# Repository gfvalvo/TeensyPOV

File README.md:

# TeensyPOV:

## POV Project on Teensy 3.2 - WORK IN PROGRESS

Library for POV (Persistence of Vision) display using Teensy 3.2 board and Adafuit DotStar LEDs (APA102). Descriptions of the hardware (including schematics and PWB) are in the Hardware folder.
The library is configured to support up to 48 LEDs in the string and up to 512 angular positions (~0.7 degree resolution). These positions are referred to as "segments" in the code and description below.
## Sample Images:

[Video of POV in Action](https://youtu.be/CiRSouhlJos)

Note that interaction between the video's frame rate and the LED refresh rate causes some artifacts that aren't really there when you view the POV in person.

## Library Description:
Code in this library directly manipulates the Teensy processor's Programmable Interrupt Timers. Thus, it is incompatible with any code that uses these timers directly or indirectly via the Teensyduino IntervalTimer class.

All of the following class methods are demonstrated in the example sketches.
### Classes:
#### Class TeensyPOV
This class interfaces with the hardware and controls the LEDs to produce the POV display. All methods in this class are static. Thus there is no need to instantiate an object of this type.
#### Public TeensyPOV Members Functions:
****Initialize the T3.2 hardware needed for the POV Display****

    bool povSetup(uint8_t hPin, CRGB *ledPtr, uint8_t num)
**Arguments:**
 - **uint8_t hPin** - Hardware pin that the Hall Effect Sensor is connected to.
 - **CRGB \*ledPtr** - Pointer to an array of FastLED CRGB objects. These objects should be registered with the FastLED library before calling povSetup.
 - **uint8_t num** - Number LEDs in the array
 
****Check if Rotation Speed is High Enough for POV Display****

    bool rpmGood(void) 

****Get Number of Segments in the Currently Active POV Display.****

    uint16_t getNumSegments(void)

****Get Number of Teensy 3.2 PIT Ticks that Occurred During the Blade's last Rotation Period. On a 96 MHz T3.2 there are 48,000,000 Ticks per Second.****

    uint32_t getLastRotationCount(void)

****Set the color of an LED directly on the display.****

    void setPixel(uint16_t segment, uint16_t pixel, uint32_t value)

**Arguments:**

- **uint16_t segment** - Rotational segment of the LED, counted clockwise from Top Dead Center. Value between 0 and (Number of Segments)-1
- **uint16_t pixel** - Radial position of the LED, 0 = innermost.
- **uint32_t value** - Color of the LED expressed as index into current Palette.

#### Public TeensyPOV Data Members:

Defined constants that can be used in calls to TeensyPovDisplay methods (see **Class TeensyPovDisplay**):
```
static const uint8_t LOG_2_SEGMENTS = 1;
static const uint8_t LOG_4_SEGMENTS = 2;
static const uint8_t LOG_8_SEGMENTS = 3;
static const uint8_t LOG_16_SEGMENTS = 4;
static const uint8_t LOG_32_SEGMENTS = 5;
static const uint8_t LOG_64_SEGMENTS = 6;
static const uint8_t LOG_128_SEGMENTS = 7;
static const uint8_t LOG_256_SEGMENTS = 8;
static const uint8_t LOG_512_SEGMENTS = 9;

static const uint8_t COLOR_BITS_1 = 1;
static const uint8_t COLOR_BITS_2 = 2;
static const uint8_t COLOR_BITS_4 = 4;
static const uint8_t COLOR_BITS_8 = 8;
```
#### Class TeensyPovDisplay
This class allows the user to define POV images to be displayed. There can be multiple instances of this class defining different images. Only one is actively displayed at a time.
#### Public TeensyPovDisplay Members Functions:
****Constructor.****
````
TeensyPovDisplay()
````
****Load an empty TeensyPovDisplay object. Would be used if no bitmap image or text is desired. Pixels would be set by the main program using the setLed() method.****
````
void load(void)
````
****Load a TeensyPovDisplay object with a bit pattern image.****
````
void load(const LedArrayStruct *pattern)
````

**Arguments:**

- **const LedArrayStruct \*pattern** - Pointer to the image structure. The struct pointed to must be static or global. See below for definition of the LedArrayStruct structure.

****Load a TeensyPovDisplay object with text strings.****
````
void load(const DisplayStringSpec *strArray, uint8_t n)
````
**Arguments:**
- **const DisplayStringSpec \*strArray** - Pointer to an array of DisplayStringSpec structures. The array pointed to must be static or global. See below for definition of the DisplayStringSpec structure.
- **uint8_t n** - Number of DisplayStringSpec structures in the array.

****Load a TeensyPovDisplay object with a bit pattern image and text strings.****
````
void load(const LedArrayStruct *pattern, const DisplayStringSpec *strArray, uint8_t n)
````
**Arguments:**
- **const LedArrayStruct \*pattern** - Pointer to the image structure. The struct pointed to must be static or global. See below for definition of the LedArrayStruct structure.
- **const DisplayStringSpec \*strArray** - Pointer to an array of DisplayStringSpec structures. The array pointed to must be static or global. See below for definition of the DisplayStringSpec structure.
- **uint8_t n** - Number of DisplayStringSpec structures in the array.

****Display a TeensyPovDisplay object on the POV LEDs. Resets the duration and rotation timers.****
````
void activate()
````
****Refresh the TeensyPovDisplay object on the POV LEDs after changing text, bit image, palette, etc. Does not reset the duration and rotation timers****
````
void refresh()
````
****Set the POV parameters for a TeensyPovDisplay object that does not contain a bitmap image (i.e. a LedArrayStruct). Call this function after load() and before activate()****
````
void setDisplay(uint8_t logSeg, uint8_t cBits, uint16_t tdc, const uint32_t *colors)
````
**Arguments:**
- **uint8_t logSeg** - Log (base 2) of number of TDC segments. Use static constants defined by class TeensyPOV.
- **uint8_t cBits** - Number of color bits. Use static constants defined by class TeensyPOV.
- **uint16_t tdc** - Segment number to display when rotating blade hits Top Dead Center.
- **const uint32_t \*colors** - Pointer to array defining RGB color pallet. Array must have at least 2 ^ cBits elements. The array pointed to must be static or global.

****Set timing for dynamic TeensyPovDisplay objects. Calling this function is optional, all values are set to their default values by the load() method.****
````
void setTiming(uint32_t duration, uint32_t rotation, int16_t tdcDelta)
````
**Arguments:**
- **uint32_t duration** - Time (in milliseconds) before the object expires. Use zero (default) if object is permanent.
- **uint32_t rotation** - Time (in milliseconds) between changes in the Top Dead Center segment, causes display to rotate. Use zero (default)  for no rotation.
- **int16_t tdcDelta** - Adjustment to Top Dead Center segment every 'rotation' milliseconds. Use negative value for clockwise rotation and positive value for anti-clockwise. Has no effect if 'rotation' is zero.

****Determine if duration of TeensyPovDisplay object has expired and performs specified rotation****
````
bool update()
````
**Returns:** True if display's time has expired.

****Set optional callback function to be called when a TeensyPovDisplay object is activated.****
````
void setActivationCallback(void (*ptr)(TeensyPovDisplay *))
````
**Arguments:**
- **void (\*ptr)(TeensyPOV \*)** - Pointer to the function to be called. The function must take as an argument a pointer to the TeensyPOV object that was activated and return void.

****Set optional callback function to be called when a TeensyPovDisplay object is updated.****
````
void setUpdateCallback(void (*ptr)(TeensyPovDisplay *))
````
**Arguments:**
- **void (\*ptr)(TeensyPOV \*)** - Pointer to the function to be called. The function must take as an argument a pointer to the TeensyPOV object that was updated and return void.

****Set optional callback function to be called when a TeensyPovDisplay object expires.****
````
void setExpireCallback(void (*ptr)(TeensyPovDisplay *))
````
**Arguments:**
- **void (\*ptr)(TeensyPOV \*)** - Pointer to the function to be called. The function must take as an argument a pointer to the TeensyPOV object that expired and return void.

#### Enums and Structures Defined by TeensyPOV Class:
****Identifies text position at top or bottom of display.****
````
enum TextPosition {TOP, BOTTOM};
````
****Specification for character string to be displayed.****
````
struct DisplayStringSpec {
	const char *characters;
	TextPosition position;
	uint8_t topRow;
	uint8_t textColor;
	uint8_t backgroundColor;
	bool invert;
};
````
- **const char \*characters** - Pointer to null-terminated char array.
- **TextPosition position** - Position where text will be displayed.
- **uint8_t topRow** - LED position (from center) for top row of characters. Minimum value is 6.
- **uint8_t textColors** - Color of text expressed as index into current Palette.
- **uint8_t backgroundColor** - Background color for text expressed as index into current Palette.
- **bool invert** - Flip text on bottom so it appears right-side-up.

****Specification for bit map image to be displayed.****
````
struct LedArrayStruct {
	const uint32_t *array;
	const uint32_t *colors;
	uint32_t numColorBits;
	uint8_t logNumSegments;
	uint32_t columns;
	uint32_t tdcDisplaySegment;
};
````
- **const uint32_t \*array** - Pointer to 2-dimensional bit map array. See below for specification. The array pointed to must be static or global.
- **const uint32_t \*colors** - Pointer to array defining RGB color pallet. Array must have at least 2 ^ numColorBits elements. The array pointed to must be static or global. 
- **uint32_t numColorBits** - Number of color bits. Use static constants defined by class TeensyPOV.
- **uint8_t logNumSegments** - Log (base 2) of number of TDC segments. Use static constants defined by class TeensyPOV.
- **uint32_t columns** - Number of columns in the array.
- **uint32_t tdcDisplaySegment** - Segment number to display when rotating blade hits Top Dead Center.
- 
****Bit Map Array****

The number of Rows is equal to the number of segments in the display. The number of Columns depends on how many color bits are used to represent each LED. For example, with 36 LEDs, Two Bits / LED, and 256 Segments:

## POV Hardware:
### Block Diagram:

### PWB Schematic:

### PWB Layout:

### Populated PWB:

### Blank Blade with Hub Mounted:

### Backside Components:

### Hall Sensor:

### LEDs Mounted:

### Start with this Fan
[$20 From Target](https://www.target.com/p/holmes-174-20-3-speed-box-fan-black-hbf2001d-b/-/A-15024768)

### Reverse these Rails as Shown to Push Motor Further out the Back.

### Reverse these Brackets as Shown to Push Motor Further out the Back.

### Hall device senses magnet and signal processor that LEDs are in the Top Dead Center position.

# CREDITS
I shamelessly appropriated the Dot Matrix characters that Arduino Forum user @Jiggy-Ninja developed for his POV project posted here:
[Dram Queen](https://forum.arduino.cc/index.php?topic=493075.0)

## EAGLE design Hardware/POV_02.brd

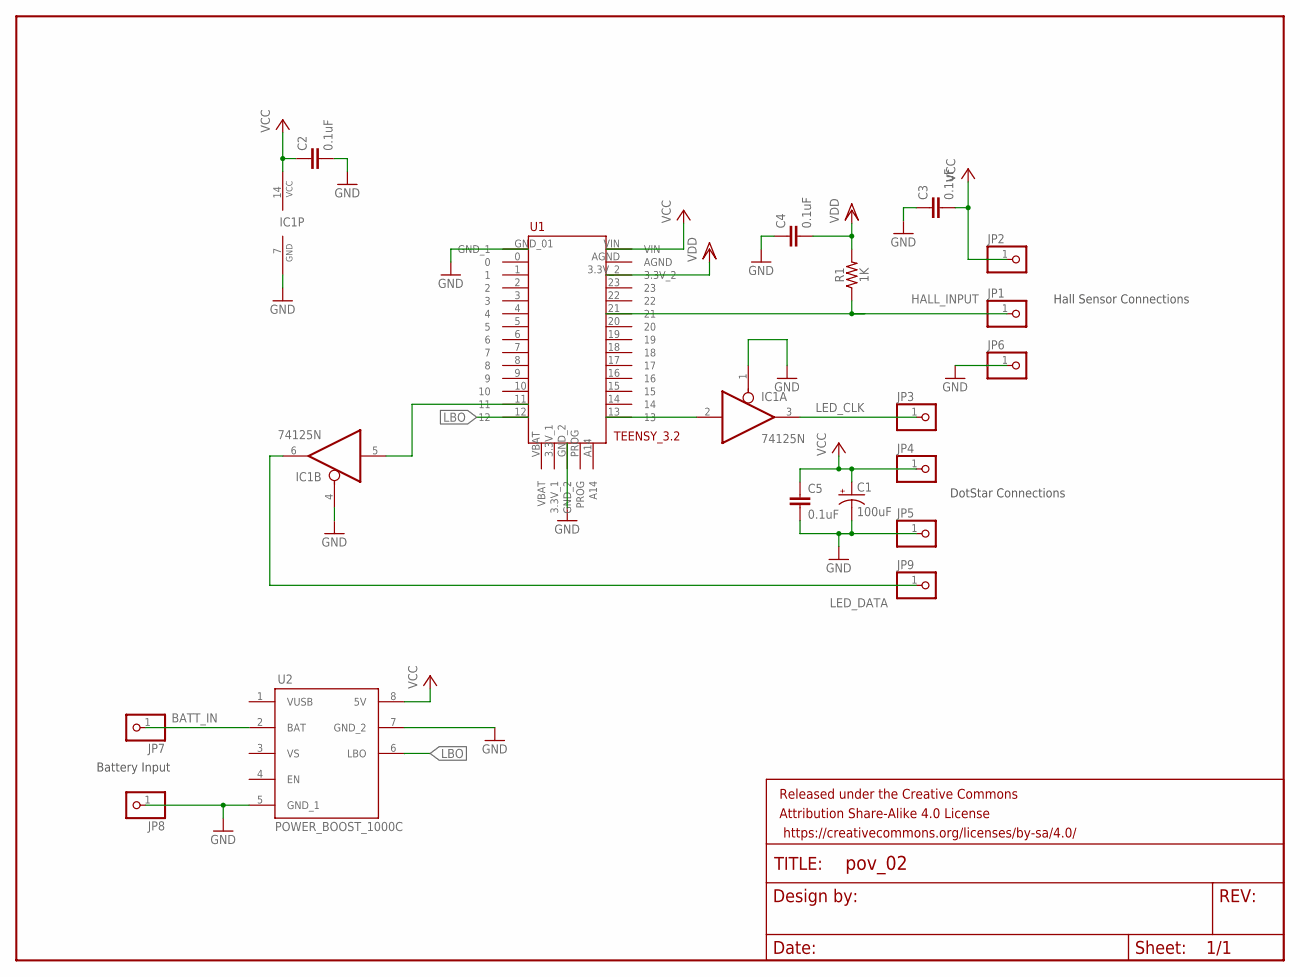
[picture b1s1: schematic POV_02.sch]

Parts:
C1: 100uF; CPOL-RADIAL-2.5MM-6.5MM
C2, C3, C4, C5: 0.1uF; CAP-PTH-SMALL-KIT
FRAME1: FRAME-LETTERNO_PACKAGE; DUMMY
IC1: 74125N; DIL14
JP1, JP2, JP3, JP4, JP5, JP6, JP7, JP8, JP9: HEADER-1X1ROUND; 1X01_ROUND
R1: 1K; AXIAL-0.3
U1: TEENSY_3.2; TEENSEY_3.2
U2: POWER_BOOST_1000C

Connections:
BATT_IN: JP7.1, U2.2 (BAT)
GND: C1.2 (-), C2.2, C3.1, C4.1, C5.2, IC1.1 (OE), IC1.4 (OE), IC1.7 (GND), JP5.1, JP6.1, JP8.1, U1.GND_01 (GND_1), U1.GND_2, U2.5 (GND_1), U2.7 (GND_2)
HALL_INPUT: JP1.1, R1.P$1 (1), U1.21
LBO: U1.12, U2.6 (LBO)
LED_CLK: IC1.3 (O), JP3.1
LED_DATA: IC1.6 (O), JP9.1
unnamed: IC1.2 (I), U1.13
unnamed: IC1.5 (I), U1.11
VCC: C1.1 (+), C2.1, C3.2, C5.1, IC1.14 (VCC), JP2.1, JP4.1, U1.VIN, U2.8 (5V)
VDD: C4.2, R1.P$2 (2), U1.3.3V_2

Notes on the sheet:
Battery Input
DotStar Connections
Hall Sensor Connections

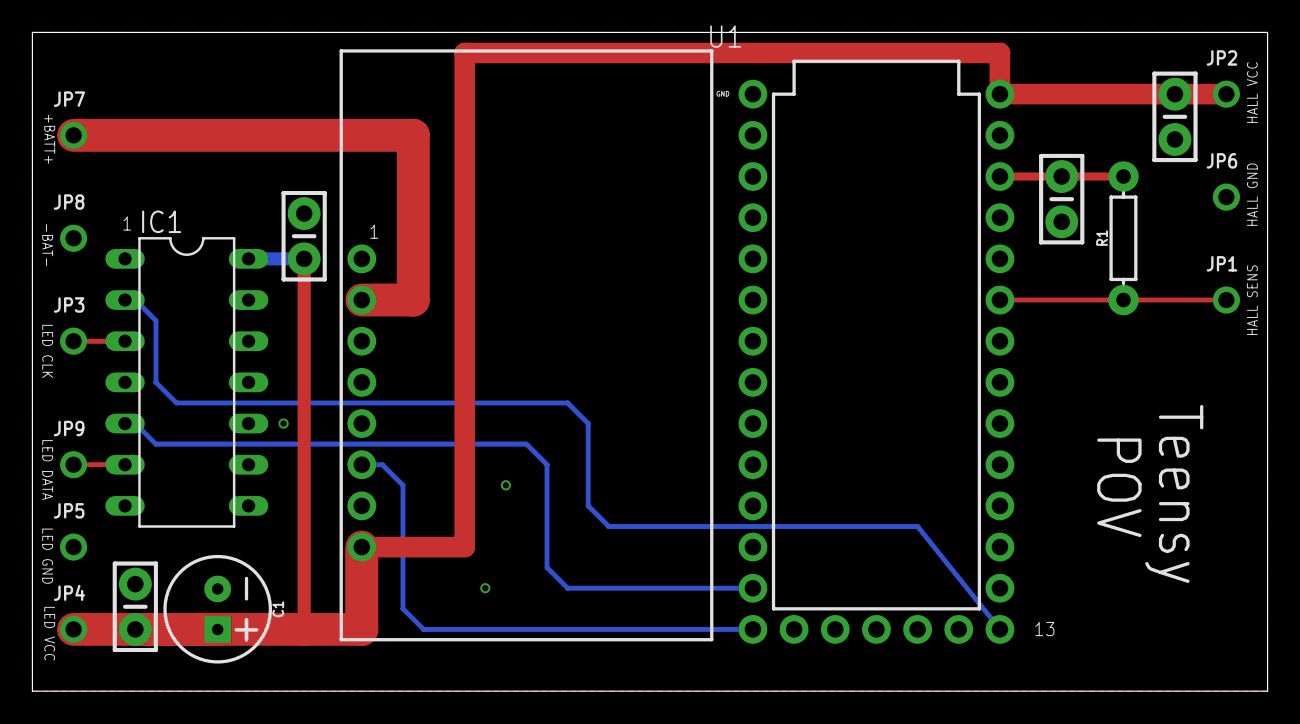
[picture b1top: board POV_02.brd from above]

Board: 2 copper layers, 76.2 x 40.6 mm, 19 parts (0 on the bottom side), 10 nets.

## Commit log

2018-04-17 Refinements, added comments to methods, added Cardioid display.
2018-04-18 More updates, added Callbacks.
2018-04-18 More updates. Modified callbacks, activate(), and refresh().
2018-04-18 Updated polar displays. Refinements.
2018-04-19 Updated example. Added comments.
2018-04-19 Preparing for library conversion.
2018-04-19 Converting to library.
2018-04-19 Renamed example to .ino file
2018-04-19 Debugging library configuration.
2018-04-19 More debug.
2018-04-19 Sloeber #pragma
2018-04-19 More library work.
2018-04-19 Update Example
2018-04-19 Updating Examples
2018-04-19 Update Examples
2018-04-20 Restructure Folders
2018-04-20 Updated Examples
2018-04-25 Update Example. Change simulation RPM.
2018-04-27 Starting new segment technique.
2018-04-27 Continue Log Segment implementation.
2018-04-27 Continue Log Segment implemenation.
2018-04-27 Finished new segment technique, updated examples.
2018-04-29 Implementing Static Class for POV
2018-04-29 Continue implementing static class for POV.
2018-04-29 Continue class update.
2018-04-29 Continue update.
2018-04-29 Updated examples.
2018-04-29 Fixed Example
2018-04-30 Updated to new color bits scheme.
2018-05-09 Modified tdcSegment update methode. Updated hallPin in examples.
2018-05-09 Added README
2018-05-12 Adding Images
2018-05-13 Updated Read Me.
2018-05-13 Updated Read Me
2018-05-16 Updated Bit Map Format Image
2018-05-22 Fix to handle 8 bits / pixel

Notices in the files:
parts and their libraries:
SparkFun-Capacitors: Licensing: Creative Commons ShareAlike 4.0 International - https://creativecommons.org/licenses/by-sa/4.0
microbuilder: This work is placed in the public domain, and may be freely used for commercial and non-commercial work with the following conditions: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
